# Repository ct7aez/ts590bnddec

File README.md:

# ts590bnddec
Arduino based KNW TS-590 Band Decoder.
This is the pcb and sch design for the TS-590S(G) Arduino based Band Decoder.
Based on the ground breaking work from Ondrej Kolonicny, OK1CDJ.
Made by João Cunha Lopes, CT2HME and Pedro Correia, CT7AEZ.
This device can read from the radio serial port is frequency and gives the Yaesu BCD and ICOM voltage output.  It has already implementations for the I2C protocol in ways to communicate with other devices like an switch box or relay driver.
Also you can connect a LCD display (arduino LiquidCrystal or I2C).
There are four buttons that can be used for the config menu.

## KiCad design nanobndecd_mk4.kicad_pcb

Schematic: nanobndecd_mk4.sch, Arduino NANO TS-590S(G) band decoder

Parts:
C1, C2: 4n7; C_0805_HandSoldering
C3: 330n; C_1812_HandSoldering
C4: 100n; C_0805_HandSoldering
C5: 220u; C_Radial_D5_L11_P2.5
C6, C8, C9, C10, C11, C12, C13, C14, C21, C22, C23, C24: 10n; C_0805_HandSoldering
C7: 2u2; C_Radial_D5_L11_P2.5
C15, C16, C17, C18, C19: 1u; C_Radial_D5_L11_P2.5
CON1: 5,5/2,1mm; BARREL_JACK
D1, D2, D4, D5: 1N5817; Diode_DO-41_SOD81_Horizontal_RM10
D3: 1.5KE20A; Diode_DO-201AD_Horizontal_RM15
D6: 1N959B; Diode_DO-35_SOD27_Horizontal_RM10
F1: 500mAT; Fuseholder5x20_horiz_open_inline_Type-I
J1, J2: RJ45; RJ45_8
J3: DB9; DB9FC
JP1: Jumper_NC_Small; Pin_Header_Straight_1x02
L1, L2: 100u; Choke_Horizontal_RM10mm
P1, P2: CONN_01X16; Socket_Strip_Straight_1x16
P3: CONN_02X08; Pin_Header_Straight_2x08
P4: CONN_01X04; Pin_Header_Straight_1x04
Q1, Q2: BS170; TO-92_Inline_Wide
R1: 12K; R_0805_HandSoldering
R2: 20K; R_0805_HandSoldering
R3: 240R; R_0805_HandSoldering
R4, R5: 2K; R_0805_HandSoldering
RV1: 10K; Potentiometer_Trimmer-Piher-PT15-h2-5_vertical
SW1: DOWN; SW_SPST_PTS645
SW2: UP; SW_SPST_PTS645
SW3: SELECT; SW_SPST_PTS645
SW4: ESC; SW_SPST_PTS645
U1: LM7805CT; TO-220_Neutral123_Vertical_LargePads
U2: MAX232; DIP-16__300_ELL

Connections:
+5V: C19.1, D4.2, D5.2, J1.6, P3.2, P3.15, P4.3, R4.1, R5.1, RV1.1, U2.16 (VCC)
+5VA: D5.1, P2.4
+5VD: C4.1, C5.1, D4.1, U1.3
/13,8V: C2.1, D1.1, J2.6
/ACC2_PWM: P1.9, Q1.2
/BCKL: P2.11, Q2.2
/BCKLa: P3.16, Q2.1
/BND_A: C12.1, J2.1, P2.5
/BND_B: C9.1, J2.3, P2.6
/BND_C: C13.1, J2.5, P2.7
/BND_D: C10.1, J2.7, P2.8
/D2: P1.5, P3.14
/D3: P1.6, P3.13
/D4: P1.7, P3.12
/D5: P1.8, P3.11
/D11: P1.14, P3.6
/D12: P1.15, P3.4
/EXT_SCL: C11.1, J1.5, P2.10, P4.2, R5.2
/EXT_SDA: C14.1, J1.4, P2.9, P4.1, R4.2
/ICOM_BND: C6.1, C7.1, D6.2, J2.4, R1.1, R3.1
/RX: P1.2, U2.12 (R1OUT)
/RX232: C21.2, L2.1, U2.13 (R1IN)
/SW1: P1.10, P3.7, SW1.1
/SW2: P1.11, P3.8, SW2.1
/SW3: P1.12, P3.9, SW3.1
/SW4: P1.13, P3.10, SW4.1
/TX: P1.1, U2.11 (T1IN)
/TX232: C22.2, L1.1, U2.14 (T1OUT)
/TX_ENBL: C8.1, J2.2, P2.15
/VO: P3.3, RV1.2
GND: C1.2, C2.2, C3.2, C4.2, C5.2, C6.2, C7.2, C8.2, C9.2, C10.2, C11.2, C12.2, C13.2, C14.2, C17.2, C18.1, C19.2, C21.1, C22.1, C23.2, C24.2, CON1.2, D3.1, D6.1, J1.3, J2.8, J3.5, P1.4, P2.2, P3.1, P3.5, P4.4, Q2.3, R2.2, RV1.3, SW1.2, SW2.2, SW3.2, SW4.2, U1.2, U2.15 (GND)
unnamed: C1.1, CON1.1, D2.1
unnamed: C15.1, U2.1 (C1+)
unnamed: C15.2, U2.3 (C1-)
unnamed: C16.1, U2.4 (C2+)
unnamed: C16.2, U2.5 (C2-)
unnamed: C17.1, U2.2 (V+)
unnamed: C18.2, U2.6 (V-)
unnamed: C23.1, J3.3, J3.6, L1.2
unnamed: C24.1, J3.1, J3.2, L2.2
unnamed: D1.2, D2.2, F1.1
unnamed: J3.7, JP1.1
unnamed: J3.8, JP1.2
unnamed: P2.12, R1.2, R2.1
unnamed: Q1.3, R3.2
VCC: C3.1, D3.2, F1.2, P2.1, Q1.1, U1.1

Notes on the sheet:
Arduino NANO goes here
Max. 19VDC Min. 9VDC
Use JP2 when using a stock straigth cable
1-D1/TX--TX 2-D0/RX--RX 3-RESET--RESET 4-GND--GND 5-D2--DISPLAY D7 (OUT) 6-D3--DISPLAY D6 (OUT) 7-D4--DISPLAY D5 (OUT) 8-D5--DISPLAY D4 (OUT) 9-D6--ACC_PWM (OUT PWM) 10-D7--SW1 DOWN (INP) 11-D8--SW2 UP (INP) 12-D9--SW3 SELECT (INP) 13-D10--SW4 ESC (INP) 14-D11--DISPLAYENABLE (OUT) 15-D12--DISPLAY RS
30-VIN--VCC 29-GND--GND 28-RESET--RESET 27-+5V--TO +5VA (INP/OUT) 26-A0--YAESU BAND DATA A (INP/OUT) 25-A1--YAESU BAND DATA B (INP/OUT) 24-A2--YAESU BAND DATA C (INP/OUT) 23-A3--YAESU BAND DATA D (INP/OUT) 22-A4--EXT_SDA (I2C) 21-A5--EXT_SCL (I2C) 20-A6--BCKL (OUT) 19-A7--ICOM_BND (ANALOG INP) 18-A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
x .6 divider
I2C Pull Up
NSR 6 Pin
NSR 4 Pin
NSR 2 Pin

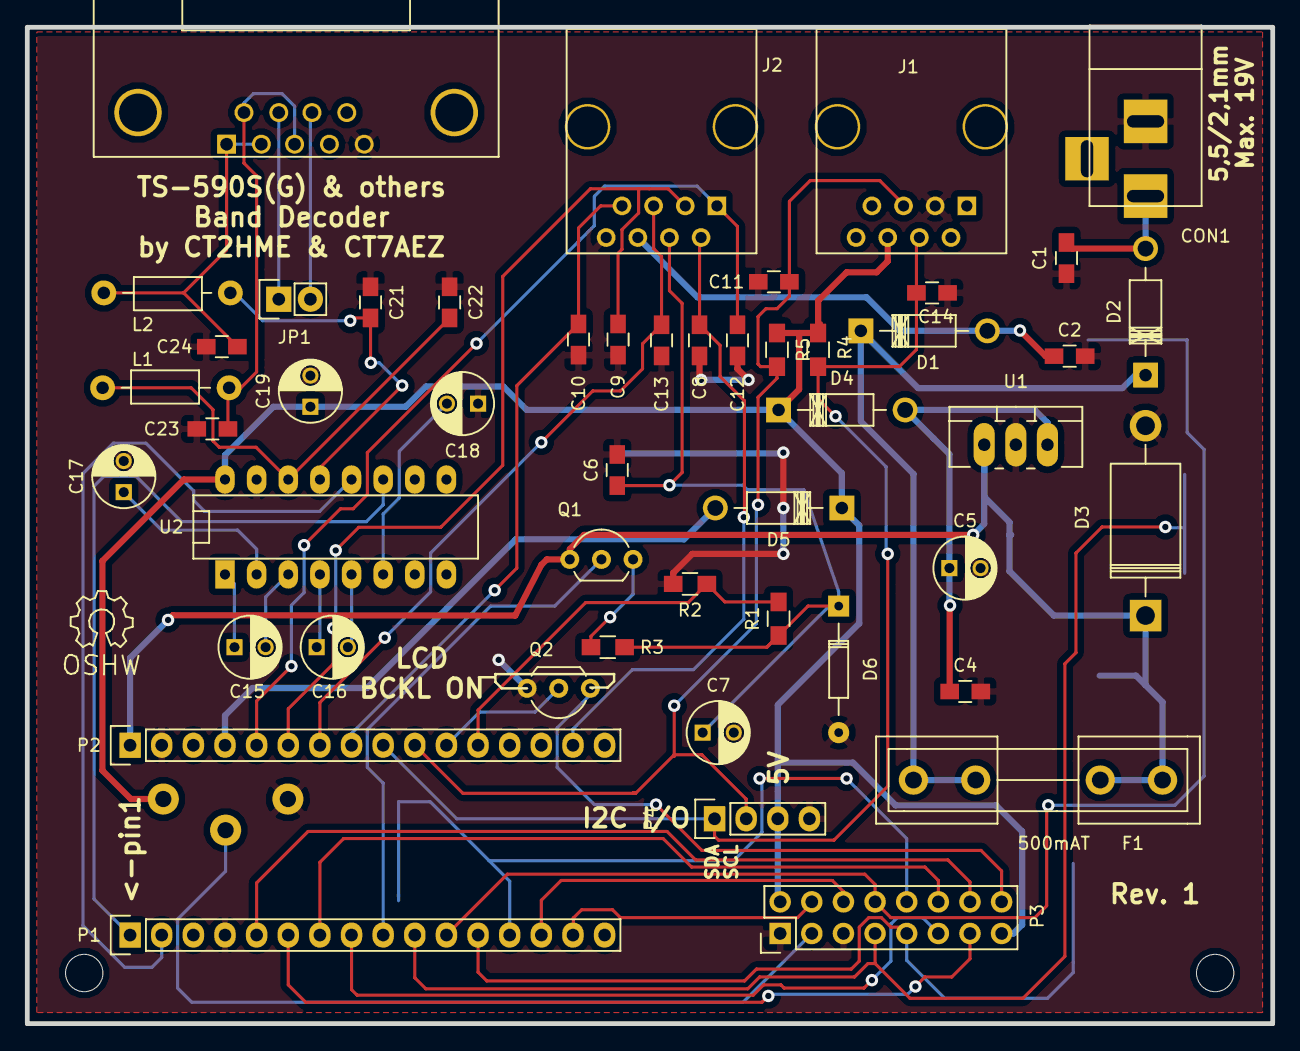
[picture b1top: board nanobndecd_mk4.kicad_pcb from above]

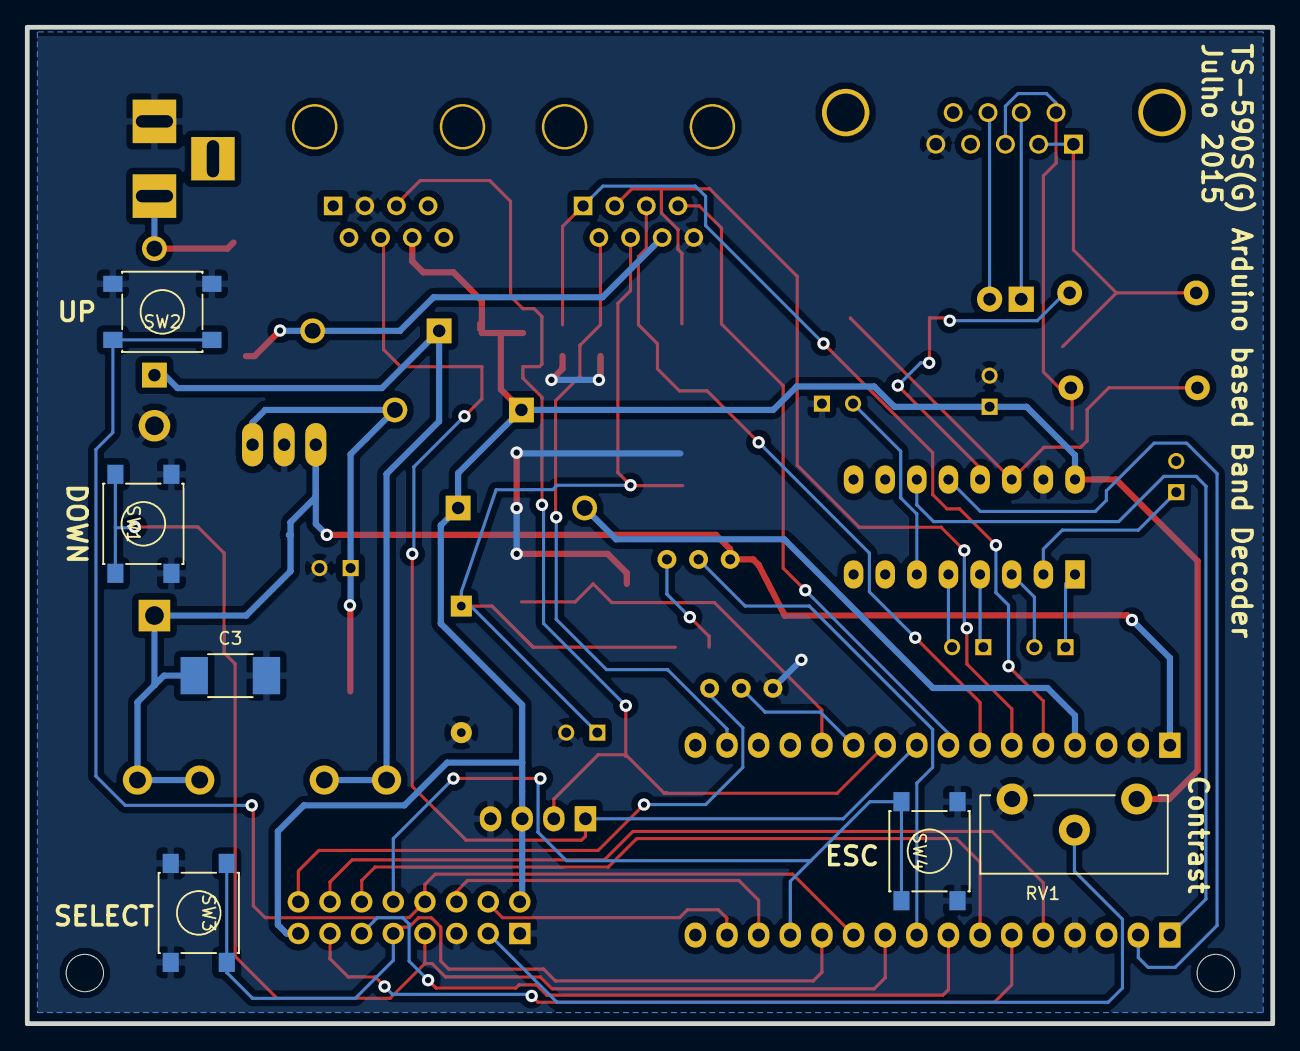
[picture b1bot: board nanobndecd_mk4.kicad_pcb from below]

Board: 2 copper layers, 100.0 x 80.0 mm, 55 parts (6 on the bottom side), 46 nets.

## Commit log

2015-07-14 kick off
2015-07-14 Ver. 1 revision for Kicad 2015-06-24 BZR 5815
2015-07-14 Final PCB
2015-07-14 Update description
2015-07-14 ignore update
2015-07-15 CC licence added
2015-07-15 CC update
2015-07-18 Corrected U1 footprint
2015-07-19 Corrected P4 to pin header
2015-07-21 proj update
2015-07-21 pcb text update

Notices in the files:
nanobndecd_mk4.kicad_pcb:
and Pedro Correia, CT7AEZ is licensed under a Creative Commons
